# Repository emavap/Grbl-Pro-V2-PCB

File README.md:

# GRBL-Pro

## License

**Creative-Commons 3.0 CC BY-SA**

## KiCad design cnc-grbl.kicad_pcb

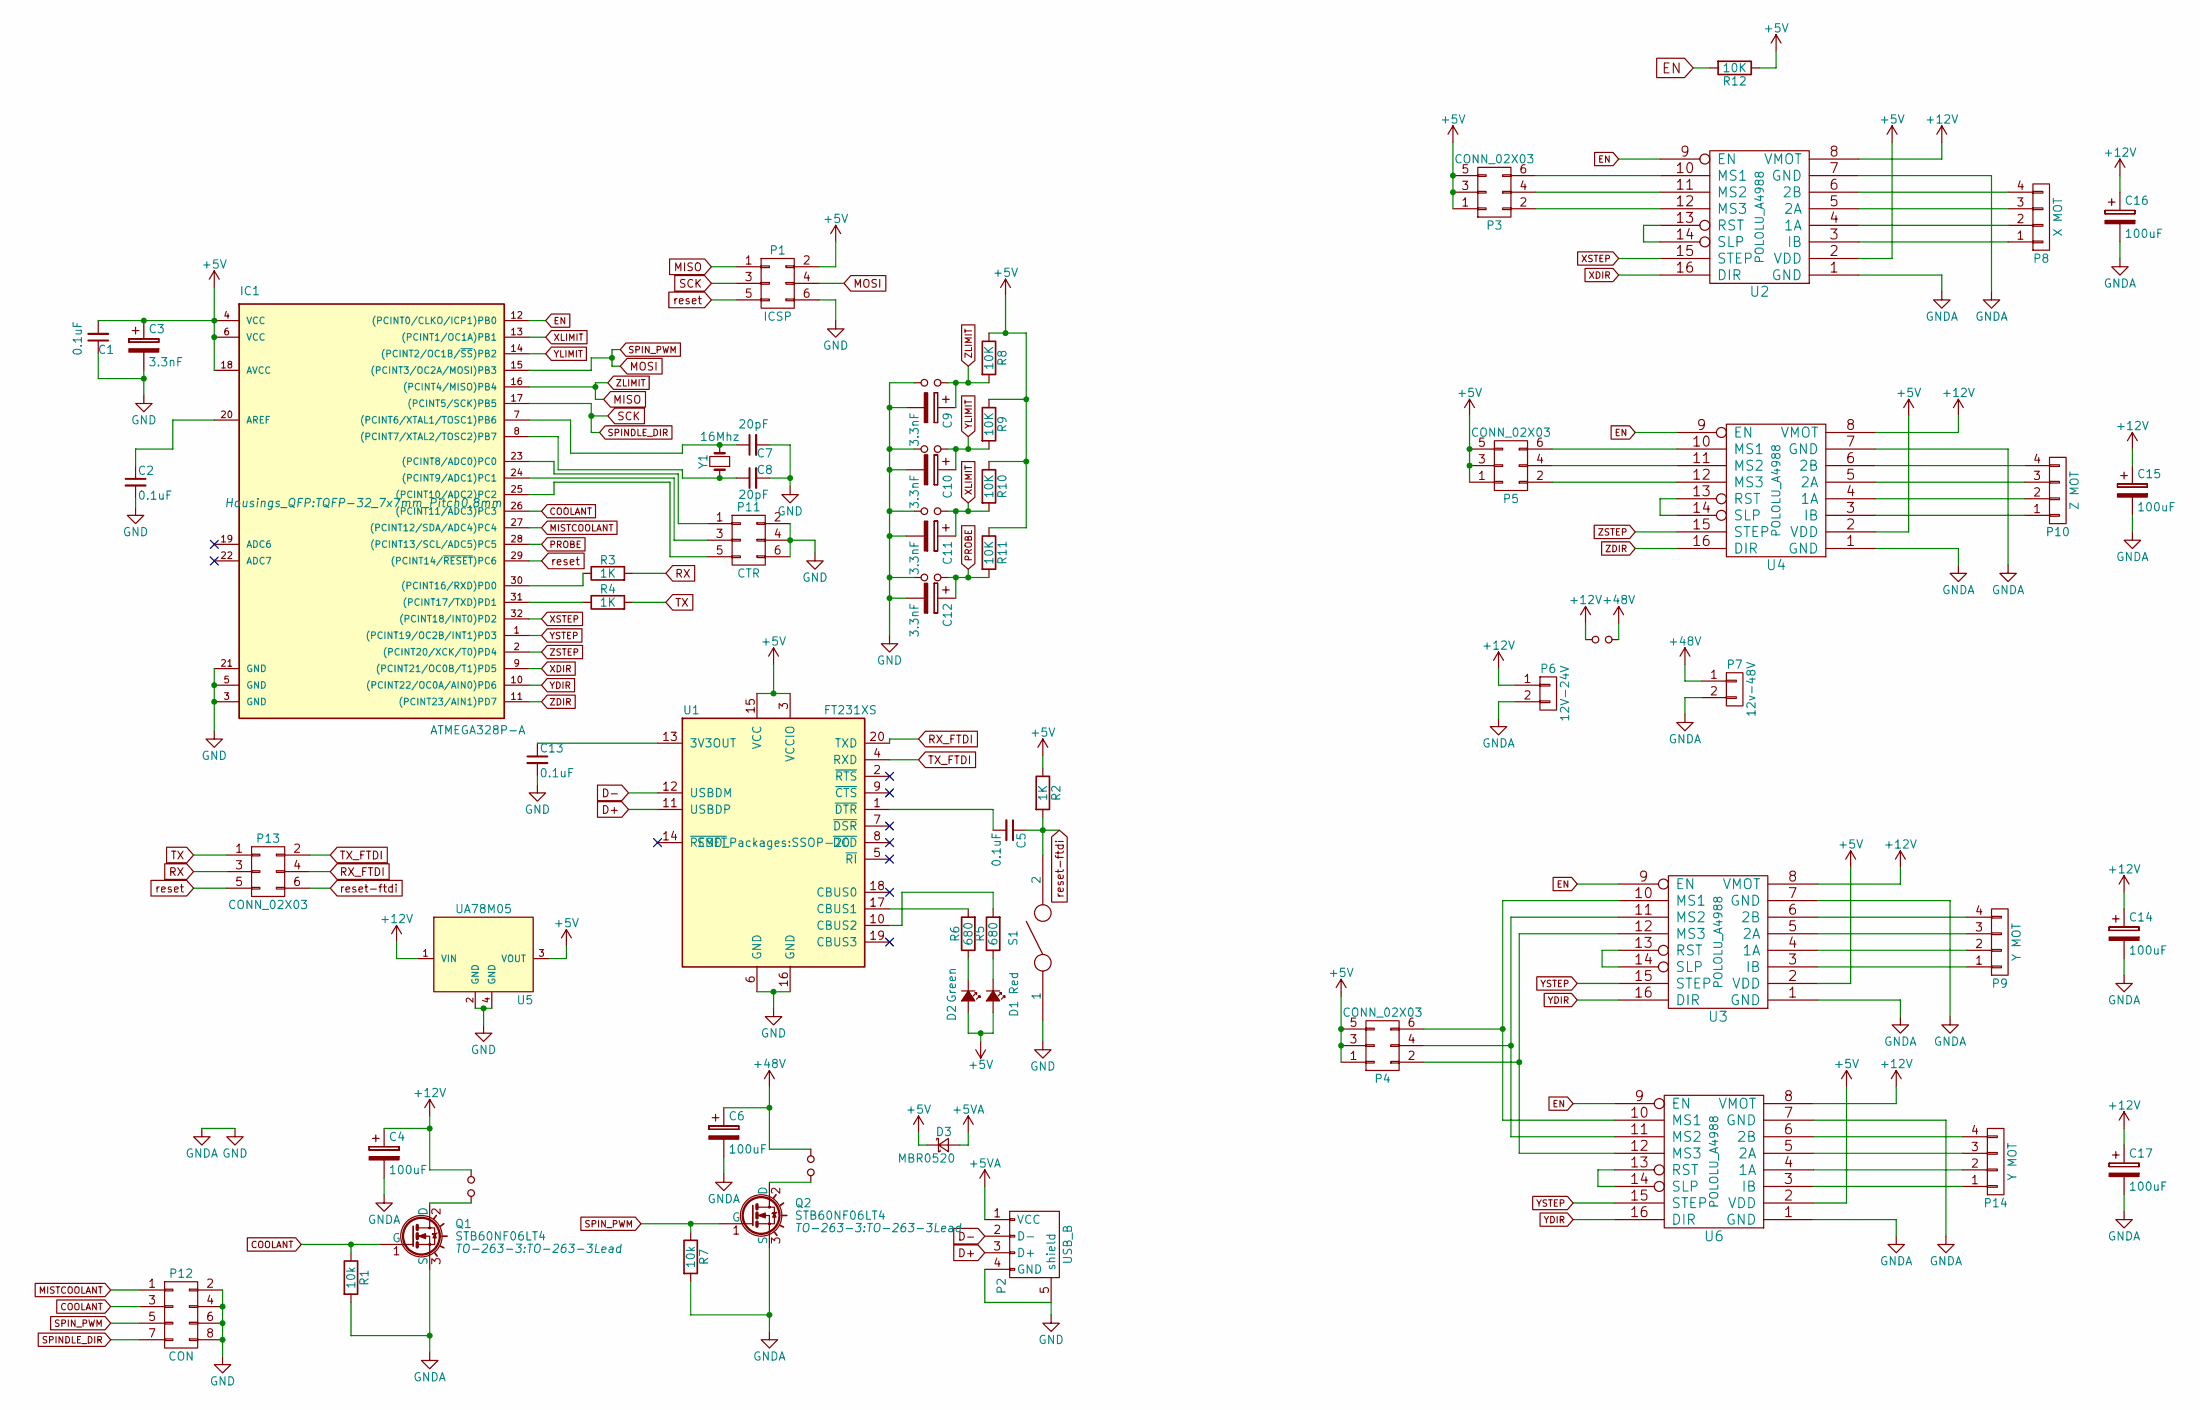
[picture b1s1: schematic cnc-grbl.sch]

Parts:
C1, C2, C5, C13: 0.1uF; C_1206
C3, C9, C10, C11, C12: 3.3nF; C_1206
C4, C6: 100uF; c_elec_6.3x7.7
C7, C8: 20pF; C_1206
C14, C15, C16, C17: 100uF; c_elec_6.3x5.3
D1: Red; LED_1206
D2: Green; LED_1206
D3: MBR0520; SOD-123
IC1: ATMEGA328P-A; TQFP-32_7x7mm_Pitch0.8mm
JP1: Fan; TerminalBlock_Pheonix_MKDS1.5-2pol
JP2: Spindle; TerminalBlock_Pheonix_MKDS1.5-2pol
JP3: Z+; TerminalBlock_Pheonix_PT-3.5mm_2pol
JP4: Y+; TerminalBlock_Pheonix_PT-3.5mm_2pol
JP5: X+; TerminalBlock_Pheonix_PT-3.5mm_2pol
JP6: Probe; TerminalBlock_Pheonix_PT-3.5mm_2pol
JP7: Jumper; Pin_Header_Straight_1x02
P1: ICSP; Pin_Header_Straight_2x03
P2: USB_B
P3, P4, P5, P13: CONN_02X03; Pin_Header_Straight_2x03
P6: 12V-24V; TerminalBlock_Pheonix_MKDS1.5-2pol
P7: 12v-48V; TerminalBlock_Pheonix_MKDS1.5-2pol
P8: X MOT; TerminalBlock_Pheonix_PT-3.5mm_4pol
P9, P14: Y MOT; TerminalBlock_Pheonix_PT-3.5mm_4pol
P10: Z MOT; TerminalBlock_Pheonix_PT-3.5mm_4pol
P11: CTR; Pin_Header_Straight_2x03
P12: CON; Pin_Header_Straight_2x04
Q1, Q2: STB60NF06LT4; TO-263-3Lead
R1, R7: 10k; R_1206
R2, R3, R4: 1K; R_1206
R5, R6: 680; R_1206
R8, R9, R10, R11, R12: 10K; R_1206
S1: SWITCH; SW_SPST_PTS645
U1: FT231XS; SSOP-20
U2, U3, U4, U6: POLOLU_A4988; Pololu_Socket
U5: UA78M05; SOT-223
Y1: 16Mhz; Crystal_HC49-SD_SMD

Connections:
+5V: C1.2, C3.1, D1.2 (A), D2.2 (A), D3.1 (K), IC1.4 (VCC), IC1.6 (VCC), IC1.18 (AVCC), P1.2, P3.1, P3.3, P3.5, P4.1, P4.3, P4.5, P5.1, P5.3, P5.5, R2.1, R8.1, R9.1, R10.1, R11.1, R12.1, U1.3 (VCCIO), U1.15 (VCC), U2.2 (VDD), U3.2 (VDD), U4.2 (VDD), U5.3 (VOUT), U6.2 (VDD)
+5VA: D3.2 (A), P2.1 (VCC)
+12V: C4.1, C14.1, C15.1, C16.1, C17.1, JP1.1, JP7.2, P6.1, U2.8 (VMOT), U3.8 (VMOT), U4.8 (VMOT), U5.1 (VIN), U6.8 (VMOT)
+48V: C6.1, JP2.1, JP7.1, P7.1
COOLANT: IC1.26 ((PCINT11/ADC3)PC3), P12.3, Q1.1 (G), R1.1
D+: P2.3 (D+), U1.11 (USBDP)
D-: P2.2 (D-), U1.12 (USBDM)
EN: IC1.12 ((PCINT0/CLKO/ICP1)PB0), R12.2, U2.9 (EN), U3.9 (EN), U4.9 (EN), U6.9 (EN)
GND: C1.1, C2.2, C3.2, C4.2, C6.2, C7.2, C8.2, C9.2, C10.2, C11.2, C12.2, C13.2, C14.2, C15.2, C16.2, C17.2, IC1.3 (GND), IC1.5 (GND), IC1.21 (GND), JP3.1, JP4.1, JP5.1, JP6.1, P1.6, P2.4 (GND), P2.5 (shield), P6.2, P7.2, P11.2, P11.4, P11.6, P12.2, P12.4, P12.6, P12.8, Q1.3 (S), Q2.3 (S), R1.2, R7.2, S1.1, U1.6 (GND), U1.16 (GND), U2.1 (GND), U2.7 (GND), U3.1 (GND), U3.7 (GND), U4.1 (GND), U4.7 (GND), U5.2 (GND), U5.4 (GND), U6.1 (GND), U6.7 (GND)
MISO: C9.1, IC1.16 ((PCINT4/MISO)PB4), JP3.2, P1.1, R8.2
MISTCOOLANT: IC1.27 ((PCINT12/SDA/ADC4)PC4), P12.1
MOSI: IC1.15 ((PCINT3/OC2A/MOSI)PB3), P1.4, P12.5, Q2.1 (G), R7.1
unnamed: C2.1, IC1.20 (AREF)
unnamed: C5.2, U1.1 (~DTR)
unnamed: C7.1, IC1.7 ((PCINT6/XTAL1/TOSC1)PB6), Y1.2
unnamed: C8.1, IC1.8 ((PCINT7/XTAL2/TOSC2)PB7), Y1.1
unnamed: C13.1, U1.13 (3V3OUT)
unnamed: D1.1 (K), R5.1
unnamed: D2.1 (K), R6.1
unnamed: IC1.23 ((PCINT8/ADC0)PC0), P11.1
unnamed: IC1.24 ((PCINT9/ADC1)PC1), P11.3
unnamed: IC1.25 ((PCINT10/ADC2)PC2), P11.5
unnamed: IC1.30 ((PCINT16/RXD)PD0), R3.1
unnamed: IC1.31 ((PCINT17/TXD)PD1), R4.1
unnamed: JP1.2, Q1.2 (D)
unnamed: JP2.2, Q2.2 (D)
unnamed: P3.2, U2.12 (MS3)
unnamed: P3.4, U2.11 (MS2)
unnamed: P3.6, U2.10 (MS1)
unnamed: P4.2, U3.12 (MS3), U6.12 (MS3)
unnamed: P4.4, U3.11 (MS2), U6.11 (MS2)
unnamed: P4.6, U3.10 (MS1), U6.10 (MS1)
unnamed: P5.2, U4.12 (MS3)
unnamed: P5.4, U4.11 (MS2)
unnamed: P5.6, U4.10 (MS1)
unnamed: P8.1, U2.3 (IB)
unnamed: P8.2, U2.4 (1A)
unnamed: P8.3, U2.5 (2A)
unnamed: P8.4, U2.6 (2B)
unnamed: P9.1, U3.3 (IB)
unnamed: P9.2, U3.4 (1A)
unnamed: P9.3, U3.5 (2A)
unnamed: P9.4, U3.6 (2B)
unnamed: P10.1, U4.3 (IB)
unnamed: P10.2, U4.4 (1A)
unnamed: P10.3, U4.5 (2A)
unnamed: P10.4, U4.6 (2B)
unnamed: P14.1, U6.3 (IB)
unnamed: P14.2, U6.4 (1A)
unnamed: P14.3, U6.5 (2A)
unnamed: P14.4, U6.6 (2B)
unnamed: R5.2, U1.10 (CBUS2)
unnamed: R6.2, U1.17 (CBUS1)
unnamed: U2.13 (RST), U2.14 (SLP)
unnamed: U3.13 (RST), U3.14 (SLP)
unnamed: U4.13 (RST), U4.14 (SLP)
unnamed: U6.13 (RST), U6.14 (SLP)
PROBE: C12.1, IC1.28 ((PCINT13/SCL/ADC5)PC5), JP6.2, R11.2
RX: P13.3, R3.2
RX_FTDI: P13.4, U1.20 (TXD)
SCK: IC1.17 ((PCINT5/SCK)PB5), P1.3, P12.7
TX: P13.1, R4.2
TX_FTDI: P13.2, U1.4 (RXD)
XDIR: IC1.9 ((PCINT21/OC0B/T1)PD5), U2.16 (DIR)
XLIMIT: C11.1, IC1.13 ((PCINT1/OC1A)PB1), JP5.2, R10.2
XSTEP: IC1.32 ((PCINT18/INT0)PD2), U2.15 (STEP)
YDIR: IC1.10 ((PCINT22/OC0A/AIN0)PD6), U3.16 (DIR), U6.16 (DIR)
YLIMIT: C10.1, IC1.14 ((PCINT2/OC1B/~SS~)PB2), JP4.2, R9.2
YSTEP: IC1.1 ((PCINT19/OC2B/INT1)PD3), U3.15 (STEP), U6.15 (STEP)
ZDIR: IC1.11 ((PCINT23/AIN1)PD7), U4.16 (DIR)
ZSTEP: IC1.2 ((PCINT20/XCK/T0)PD4), U4.15 (STEP)
reset: IC1.29 ((PCINT14/~RESET~)PC6), P1.5, P13.5
reset-ftdi: C5.1, P13.6, R2.2, S1.2

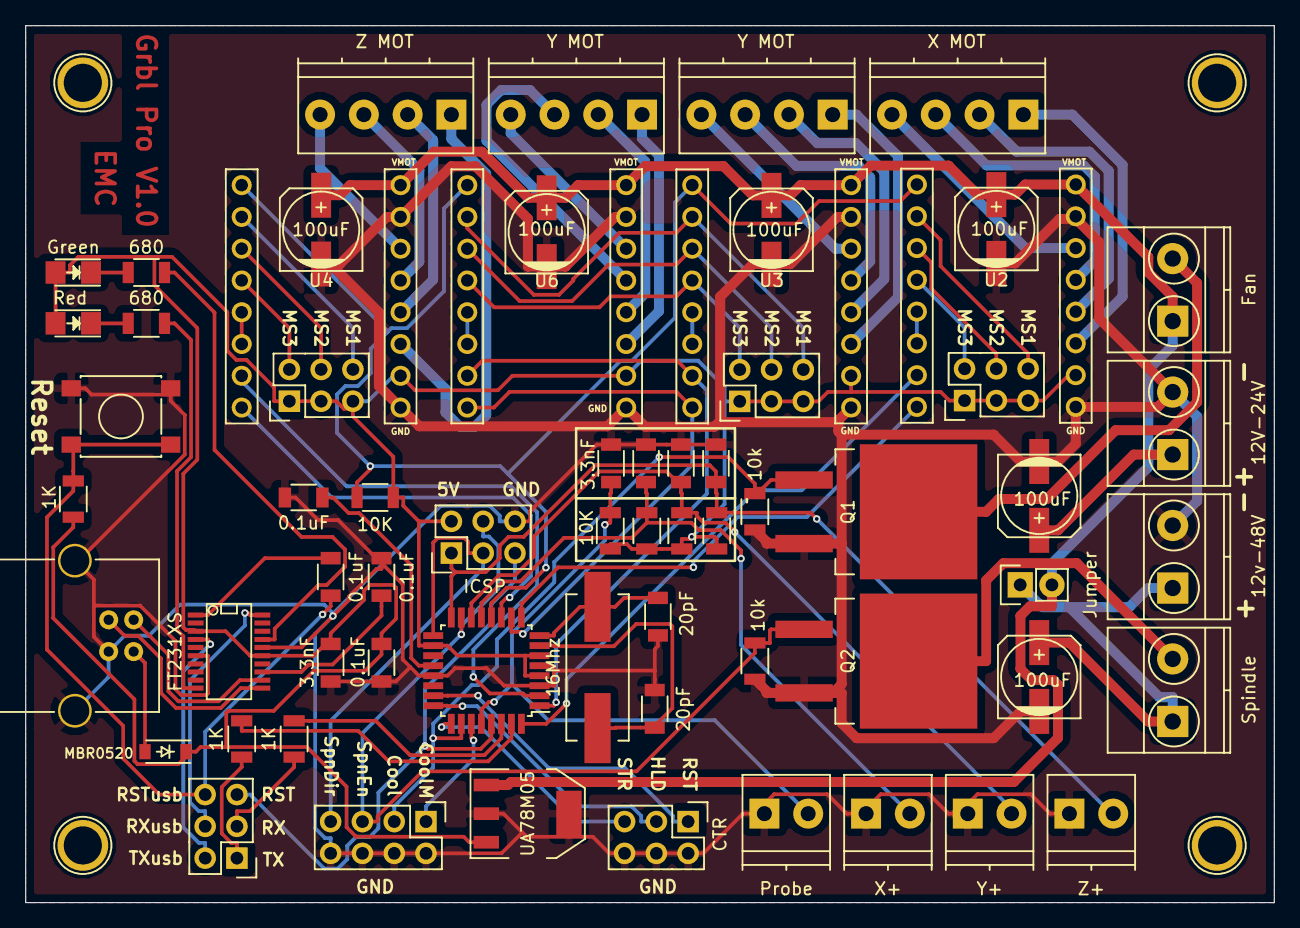
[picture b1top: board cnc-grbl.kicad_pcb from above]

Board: 2 copper layers, 99.8 x 70.1 mm, 68 parts (0 on the bottom side), 73 nets.

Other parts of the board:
REF01, REF02, REF03, REF04: 1pin

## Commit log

2017-12-17 PCB tested and working
